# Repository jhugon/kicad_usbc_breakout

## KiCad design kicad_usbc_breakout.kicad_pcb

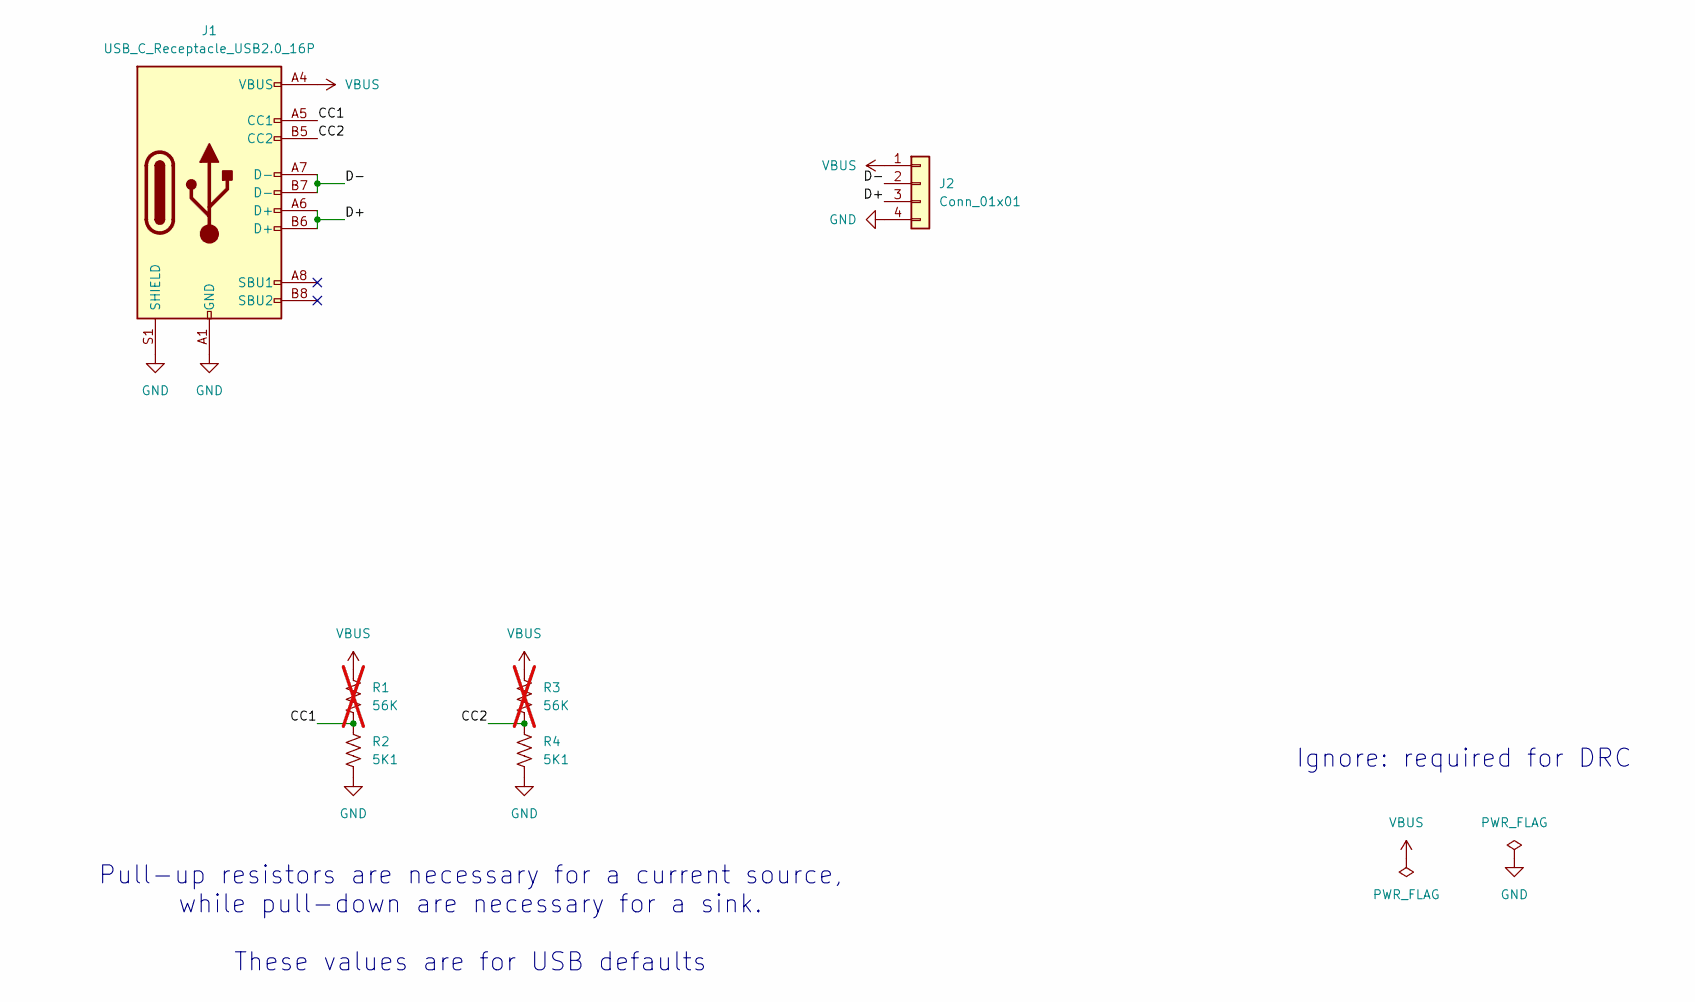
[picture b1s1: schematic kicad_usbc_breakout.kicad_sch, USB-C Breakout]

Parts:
J1: USB_C_Receptacle_USB2.0_16P; USB_C_Receptacle_GCT_USB4085_Reduced_Pad_Size; MFR Part Num USB4085-GF-A
J2: Conn_01x01; SolderWire-0.5sqmm_1x04_P4.8mm_D0.9mm_OD2.3mm_Relief
R1, R3: 56K; R_0805_2012Metric_Pad1.20x1.40mm_HandSolder; MFR Part Num CRCW080556K0FKEA; not fitted
R2, R4: 5K1; R_0805_2012Metric_Pad1.20x1.40mm_HandSolder; MFR Part Num CRCW08055K10FKEA

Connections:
/CC1: J1.A5 (CC1), R1.2, R2.1
/CC2: J1.B5 (CC2), R3.2, R4.1
/D+: J1.A6 (D+), J1.B6 (D+), J2.3
/D-: J1.A7 (D-), J1.B7 (D-), J2.2
GND: J1.A1 (GND), J1.A12 (GND), J1.B1 (GND), J1.B12 (GND), J1.S1 (SHIELD), J2.4, R2.2, R4.2
VBUS: J1.A4 (VBUS), J1.A9 (VBUS), J1.B4 (VBUS), J1.B9 (VBUS), J2.1, R1.1, R3.1

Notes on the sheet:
Pull-up resistors are necessary for a current source, while pull-down are necessary for a sink. These values are for USB defaults
Ignore: required for DRC

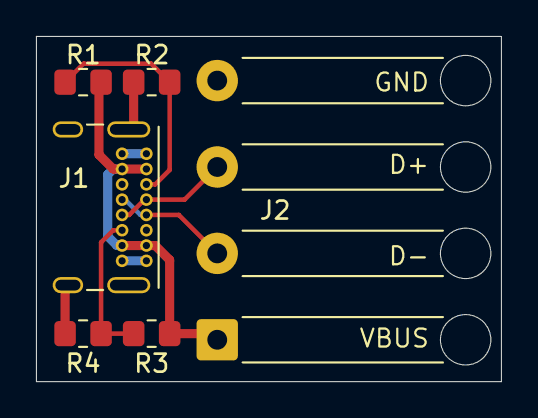
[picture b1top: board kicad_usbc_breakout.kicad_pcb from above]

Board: 2 copper layers, 25.8 x 19.2 mm, 6 parts (0 on the bottom side), 6 nets.

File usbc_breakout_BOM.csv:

"Reference","Value","Datasheet","Footprint","Qty","DNP","MFR","MFR Part Num"
"J1","USB_C_Receptacle_USB2.0_16P","https://www.usb.org/sites/default/files/documents/usb_type-c.zip","AAAA_Project_Library:USB_C_Receptacle_GCT_USB4085_Reduced_Pad_Size","1","","GCT","USB4085-GF-A"
"J2","Conn_01x01","~","Connector_Wire:SolderWire-0.5sqmm_1x04_P4.8mm_D0.9mm_OD2.3mm_Relief2x","1","","",""
"R1,R3","56K","~","Resistor_SMD:R_1206_3216Metric_Pad1.30x1.75mm_HandSolder","2","DNP","Vishay","CRCW120656K0FKEA"
"R2,R4","5K1","~","Resistor_SMD:R_1206_3216Metric_Pad1.30x1.75mm_HandSolder","2","","Vishay","CRCW12065K10FKEA"

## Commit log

2024-03-29 first pass at schematic
2024-03-29 initial pcb placement
2024-03-29 added BOM
2024-03-29 routing for pcb
2024-03-30 updated BOM with mfr and mfr part no
2024-03-30 re-placed and routed to make more compact
    also changed to 0805 resistors
2024-03-30 update BOM with 0805 r's
2024-03-30 made front silk not overlap eachother and be thick enough
2024-03-30 added renders and pdfs of sch and pcb
2024-03-30 switched around wires so that gnd and vbus are next to eachother
2024-03-30 updated all renders and pdfs to 1.1 spec
2024-04-03 added README
